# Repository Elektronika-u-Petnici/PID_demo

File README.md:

# PID demo

Ploča za demonstraciju uticaja parametara PID kontrolera.

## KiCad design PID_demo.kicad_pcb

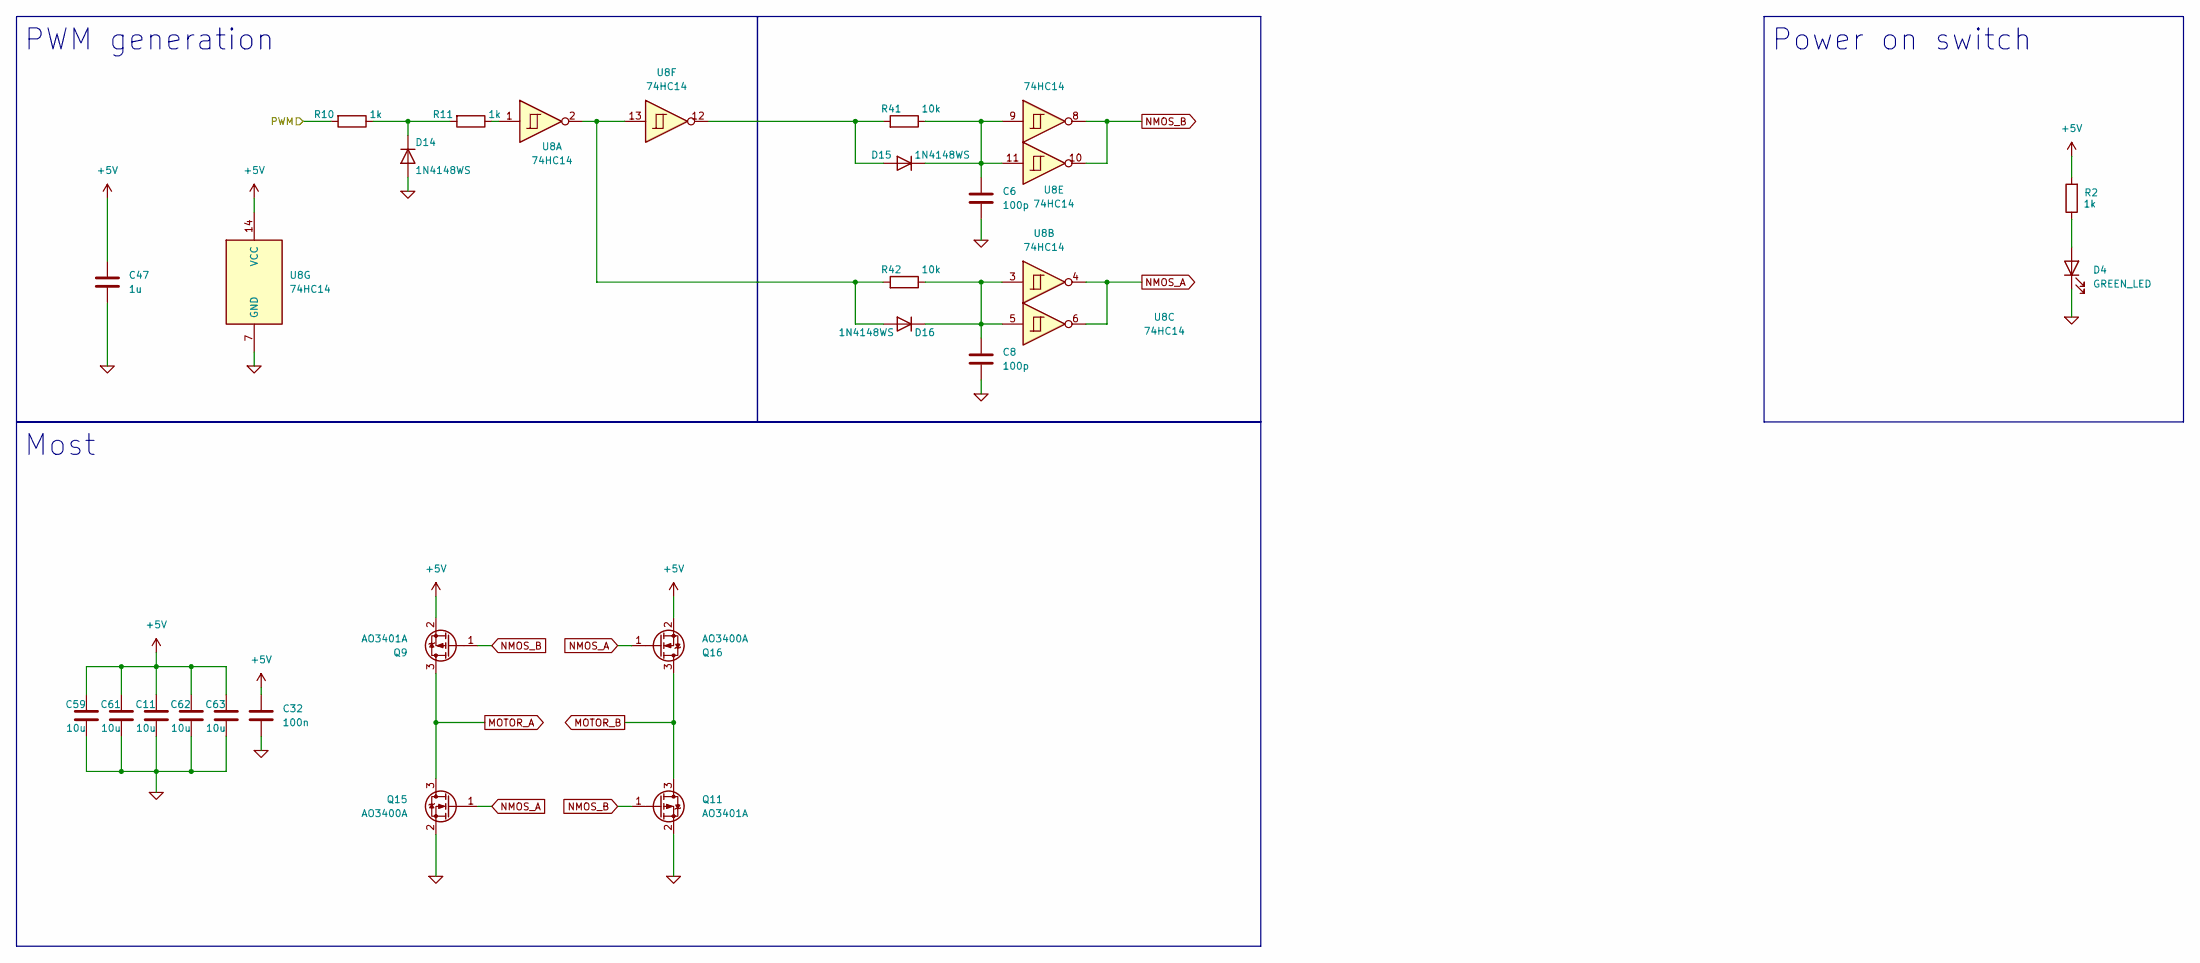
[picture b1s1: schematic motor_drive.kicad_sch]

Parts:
C6, C8: 100p; C_0603_1608Metric_Pad1.08x0.95mm_HandSolder; LCSC C14858
C11, C59, C61, C62, C63: 10u; R_0805_2012Metric_Pad1.20x1.40mm_HandSolder; Voltage 25V; LCSC C15850
C32: 100n; C_0603_1608Metric_Pad1.08x0.95mm_HandSolder; LCSC C14663
C47: 1u; C_0603_1608Metric_Pad1.08x0.95mm_HandSolder; LCSC C15849
D4: GREEN_LED; LED_0805_2012Metric_Pad1.15x1.40mm_HandSolder; LCSC C2297
D14, D15, D16: 1N4148WS; D_SOD-323; LCSC C2128
Q9, Q11: AO3401A; SOT-23; LCSC C15127
Q15, Q16: AO3400A; SOT-23; LCSC C20917
R2, R10, R11: 1k; R_0603_1608Metric_Pad0.98x0.95mm_HandSolder; LCSC C21190
R41, R42: 10k; R_0603_1608Metric_Pad0.98x0.95mm_HandSolder; LCSC C25804
U8: 74HC14; SOIC-14_3.9x8.7mm_P1.27mm

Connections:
0: C6.1, C8.1, C11.1, C32.1, C47.1, C59.1, C61.1, C62.1, C63.1, D4.1 (K), D14.2 (A), Q11.2 (S), Q15.2 (S), U8.7 (GND); also elsewhere on the board
+5V: C11.2, C32.2, C47.2, C59.2, C61.2, C62.2, C63.2, Q9.2 (S), Q16.2 (S), R2.2, U8.14 (VCC); also elsewhere on the board
/Motor drive/PWM: R10.2; also elsewhere on the board
MOTOR_A: Q9.3 (D), Q15.3 (D)
MOTOR_B: Q11.3 (D), Q16.3 (D)
NMOS_A: Q15.1 (G), Q16.1 (G), U8.4, U8.6
NMOS_B: Q9.1 (G), Q11.1 (G), U8.8, U8.10
unnamed: D4.2 (A), R2.1
unnamed: D14.1 (K), R10.1, R11.2
unnamed: D15.2 (A), R41.2, U8.12
unnamed: C6.2, D15.1 (K), R41.1, U8.9, U8.11
unnamed: D16.2 (A), R42.2, U8.2, U8.13
unnamed: C8.2, D16.1 (K), R42.1, U8.3, U8.5
unnamed: R11.1, U8.1

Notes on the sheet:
Power on switch
PWM generation
Most

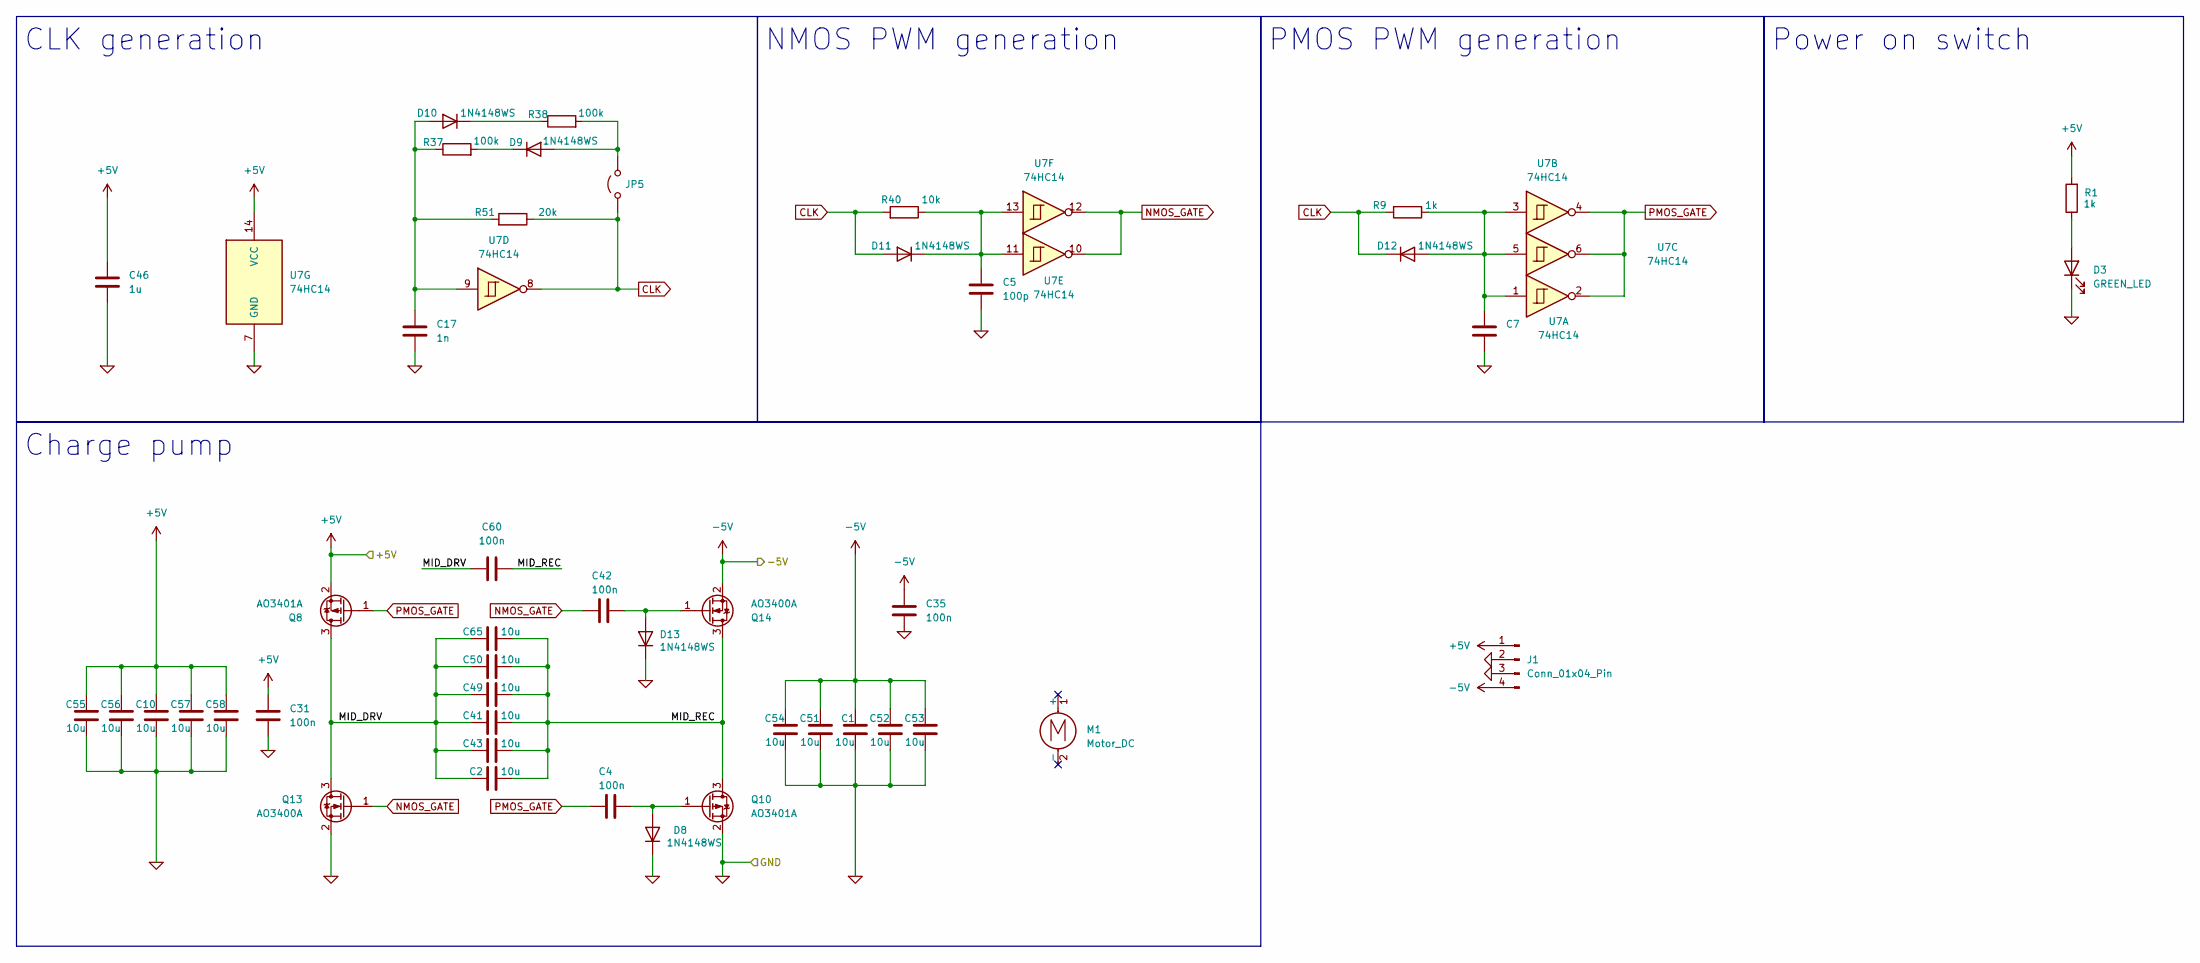
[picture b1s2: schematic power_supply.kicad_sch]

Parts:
C1, C2, C10, C41, C43, C49, C50, C51, C52, C53, C54, C55, C56, C57, C58, C65: 10u; R_0805_2012Metric_Pad1.20x1.40mm_HandSolder; Voltage 25V; LCSC C15850
C4, C31, C35, C42, C60: 100n; C_0603_1608Metric_Pad1.08x0.95mm_HandSolder; LCSC C14663
C5, C7: 100p; C_0603_1608Metric_Pad1.08x0.95mm_HandSolder; LCSC C14858
C17: 1n; C_0603_1608Metric_Pad1.08x0.95mm_HandSolder; LCSC C1588
C46: 1u; C_0603_1608Metric_Pad1.08x0.95mm_HandSolder; LCSC C15849
D3: GREEN_LED; LED_0805_2012Metric_Pad1.15x1.40mm_HandSolder; LCSC C2297
D8, D9, D10, D11, D12, D13: 1N4148WS; D_SOD-323; LCSC C2128
J1: Conn_01x04_Pin; PinHeader_1x04_P2.54mm_Vertical
JP5: Jumper_2_Open; SolderJumper-2_P1.3mm_Open_RoundedPad1.0x1.5mm
M1: Motor_DC; N20_motor
Q8, Q10: AO3401A; SOT-23; LCSC C15127
Q13, Q14: AO3400A; SOT-23; LCSC C20917
R1, R9: 1k; R_0603_1608Metric_Pad0.98x0.95mm_HandSolder; LCSC C21190
R37, R38: 100k; R_0603_1608Metric_Pad0.98x0.95mm_HandSolder; LCSC C25803
R40: 10k; R_0603_1608Metric_Pad0.98x0.95mm_HandSolder; LCSC C25804
R51: 20k; R_0603_1608Metric_Pad0.98x0.95mm_HandSolder; LCSC C4184
U7: 74HC14; SOIC-14_3.9x8.7mm_P1.27mm

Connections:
0: C1.1, C5.1, C7.1, C10.1, C17.1, C31.1, C35.1, C46.1, C51.1, C52.1, C53.1, C54.1, C55.1, C56.1, C57.1, C58.1, D3.1 (K), D8.1 (K), D13.1 (K), J1.2, J1.3, Q10.2 (S), Q13.2 (S), U7.7 (GND); also elsewhere on the board
+5V: C10.2, C31.2, C46.2, C55.2, C56.2, C57.2, C58.2, J1.1, Q8.2 (S), R1.2, U7.14 (VCC); also elsewhere on the board
-5V: C1.2, C35.2, C51.2, C52.2, C53.2, C54.2, J1.4, Q14.2 (S); also elsewhere on the board
/Charge pump/MID_DRV: C2.1, C41.1, C43.1, C49.1, C50.1, C60.2, C65.1, Q8.3 (D), Q13.3 (D)
/Charge pump/MID_REC: C2.2, C41.2, C43.2, C49.2, C50.2, C60.1, C65.2, Q10.3 (D), Q14.3 (D)
CLK: D11.2 (A), D12.1 (K), JP5.1 (A), R9.2, R40.2, R51.1, U7.8
NMOS_GATE: C42.1, Q13.1 (G), U7.10, U7.12
unnamed: D3.2 (A), R1.1
unnamed: C4.2, D8.2 (A), Q10.1 (G)
unnamed: D9.2 (A), JP5.2 (B), R38.2
unnamed: D9.1 (K), R37.2
unnamed: C17.2, D10.2 (A), R37.1, R51.2, U7.9
unnamed: D10.1 (K), R38.1
unnamed: C5.2, D11.1 (K), R40.1, U7.11, U7.13
unnamed: C7.2, D12.2 (A), R9.1, U7.1, U7.3, U7.5
unnamed: C42.2, D13.2 (A), Q14.1 (G)
PMOS_GATE: C4.1, Q8.1 (G), U7.2, U7.4, U7.6

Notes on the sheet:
Power on switch
Charge pump
CLK generation
NMOS PWM generation
PMOS PWM generation

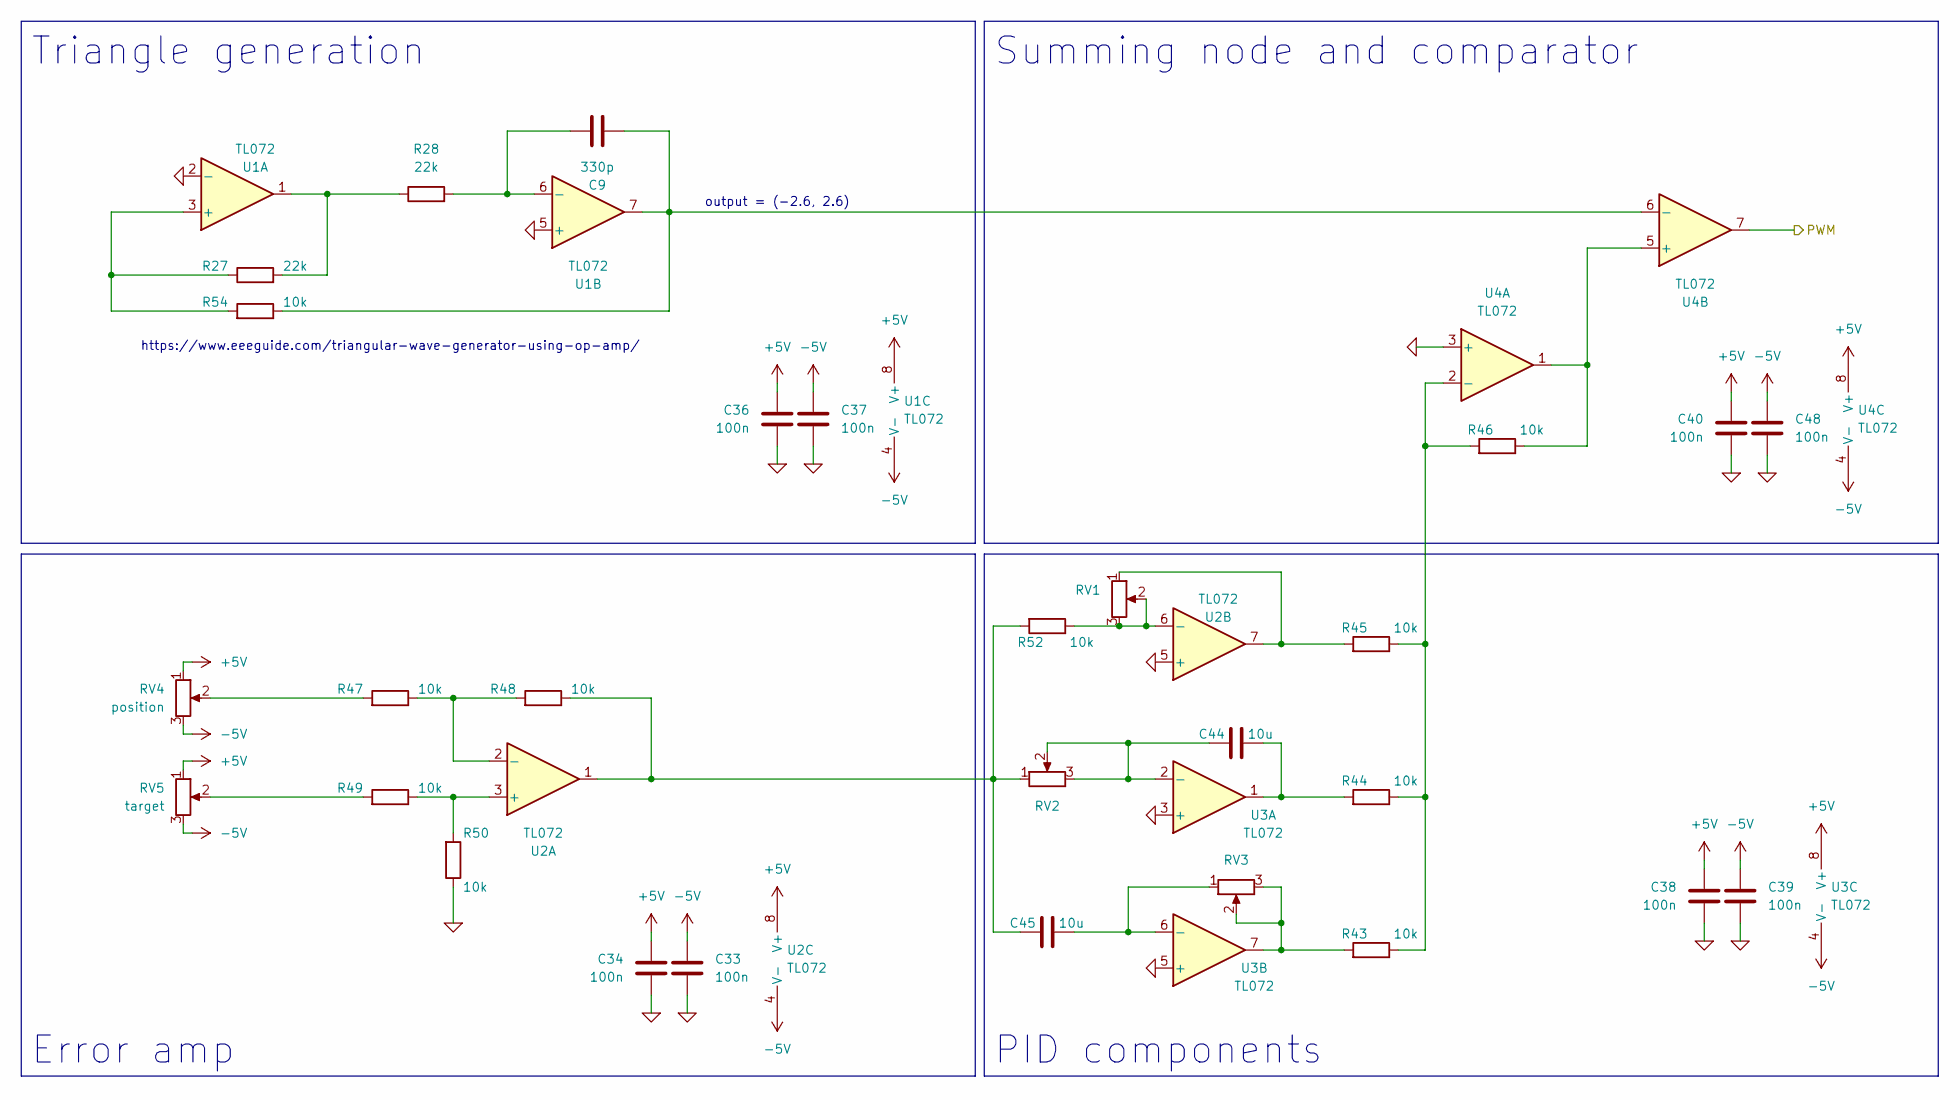
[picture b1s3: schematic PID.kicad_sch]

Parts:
C9: 330p; R_0603_1608Metric_Pad0.98x0.95mm_HandSolder; LCSC C1664
C33, C34, C36, C37, C38, C39, C40, C48: 100n; C_0603_1608Metric_Pad1.08x0.95mm_HandSolder; LCSC C14663
C44, C45: 10u; R_0805_2012Metric_Pad1.20x1.40mm_HandSolder; Voltage 25V; LCSC C15850
R27, R28: 22k; R_0603_1608Metric_Pad0.98x0.95mm_HandSolder; LCSC C31850
R43, R44, R45, R46, R47, R48, R49, R50, R52, R54: 10k; R_0603_1608Metric_Pad0.98x0.95mm_HandSolder; LCSC C25804
RV1, RV2, RV3: R_Potentiometer; front_plate_pot
RV4: position; front_plate_pot
RV5: target; front_plate_pot
U1, U2, U3, U4: TL072; SOIC-8_3.9x4.9mm_P1.27mm; LCSC C6961

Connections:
0: C33.1, C34.1, C36.1, C37.1, C38.1, C39.1, C40.1, C48.1, R50.1, U1.2 (-), U1.5 (+), U2.5 (+), U3.3 (+), U3.5 (+), U4.3 (+); also elsewhere on the board
+5V: C34.2, C36.2, C38.2, C40.2, RV4.1, RV5.1, U1.8 (V+), U2.8 (V+), U3.8 (V+), U4.8 (V+); also elsewhere on the board
-5V: C33.2, C37.2, C39.2, C48.2, RV4.3, RV5.3, U1.4 (V-), U2.4 (V-), U3.4 (V-), U4.4 (V-); also elsewhere on the board
/Motor drive/PWM: U4.7; also elsewhere on the board
unnamed: C44.2, R44.2, U3.1
unnamed: C45.1, R48.1, R52.2, RV2.1, U2.1
unnamed: R27.2, R28.1, U1.1
unnamed: R43.2, RV3.2, RV3.3, U3.7
unnamed: R45.2, RV1.1, U2.7
unnamed: R47.2, RV4.2
unnamed: R49.2, RV5.2
unnamed: R27.1, R54.2, U1.3 (+)
unnamed: C9.2, R28.2, U1.6 (-)
unnamed: R49.1, R50.2, U2.3 (+)
unnamed: R47.1, R48.2, U2.2 (-)
unnamed: R52.1, RV1.2, RV1.3, U2.6 (-)
unnamed: C44.1, RV2.2, RV2.3, U3.2 (-)
unnamed: C45.2, RV3.1, U3.6 (-)
unnamed: R43.1, R44.1, R45.1, R46.2, U4.2 (-)
unnamed: R46.1, U4.1, U4.5 (+)
unnamed: C9.1, R54.1, U1.7, U4.6 (-)

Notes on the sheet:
https://www.eeeguide.com/triangular-wave-generator-using-op-amp/
output = (-2.6, 2.6)
Error amp
Summing node and comparator
Triangle generation
PID components

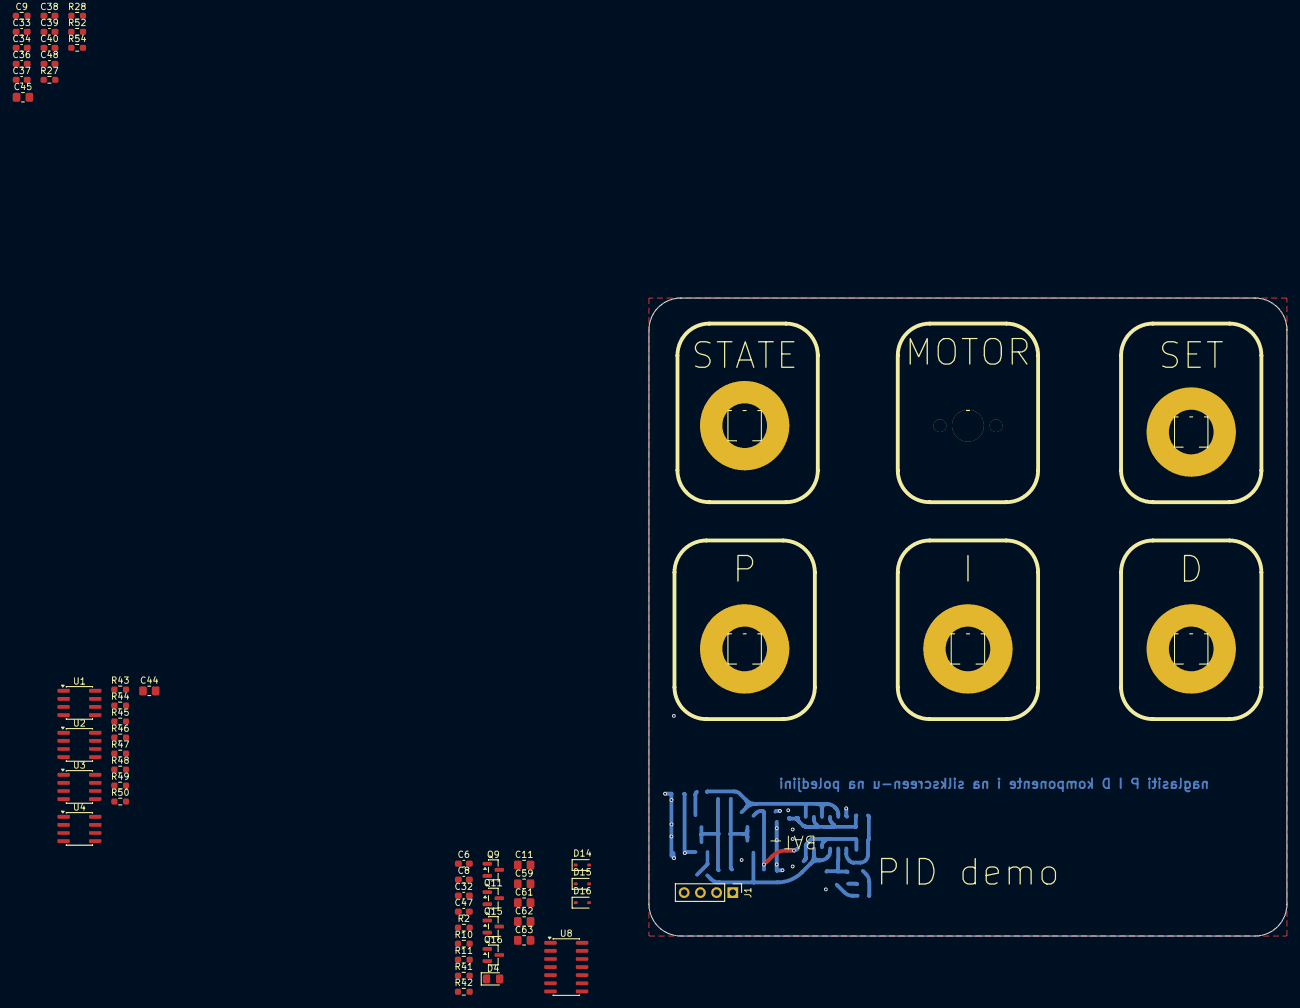
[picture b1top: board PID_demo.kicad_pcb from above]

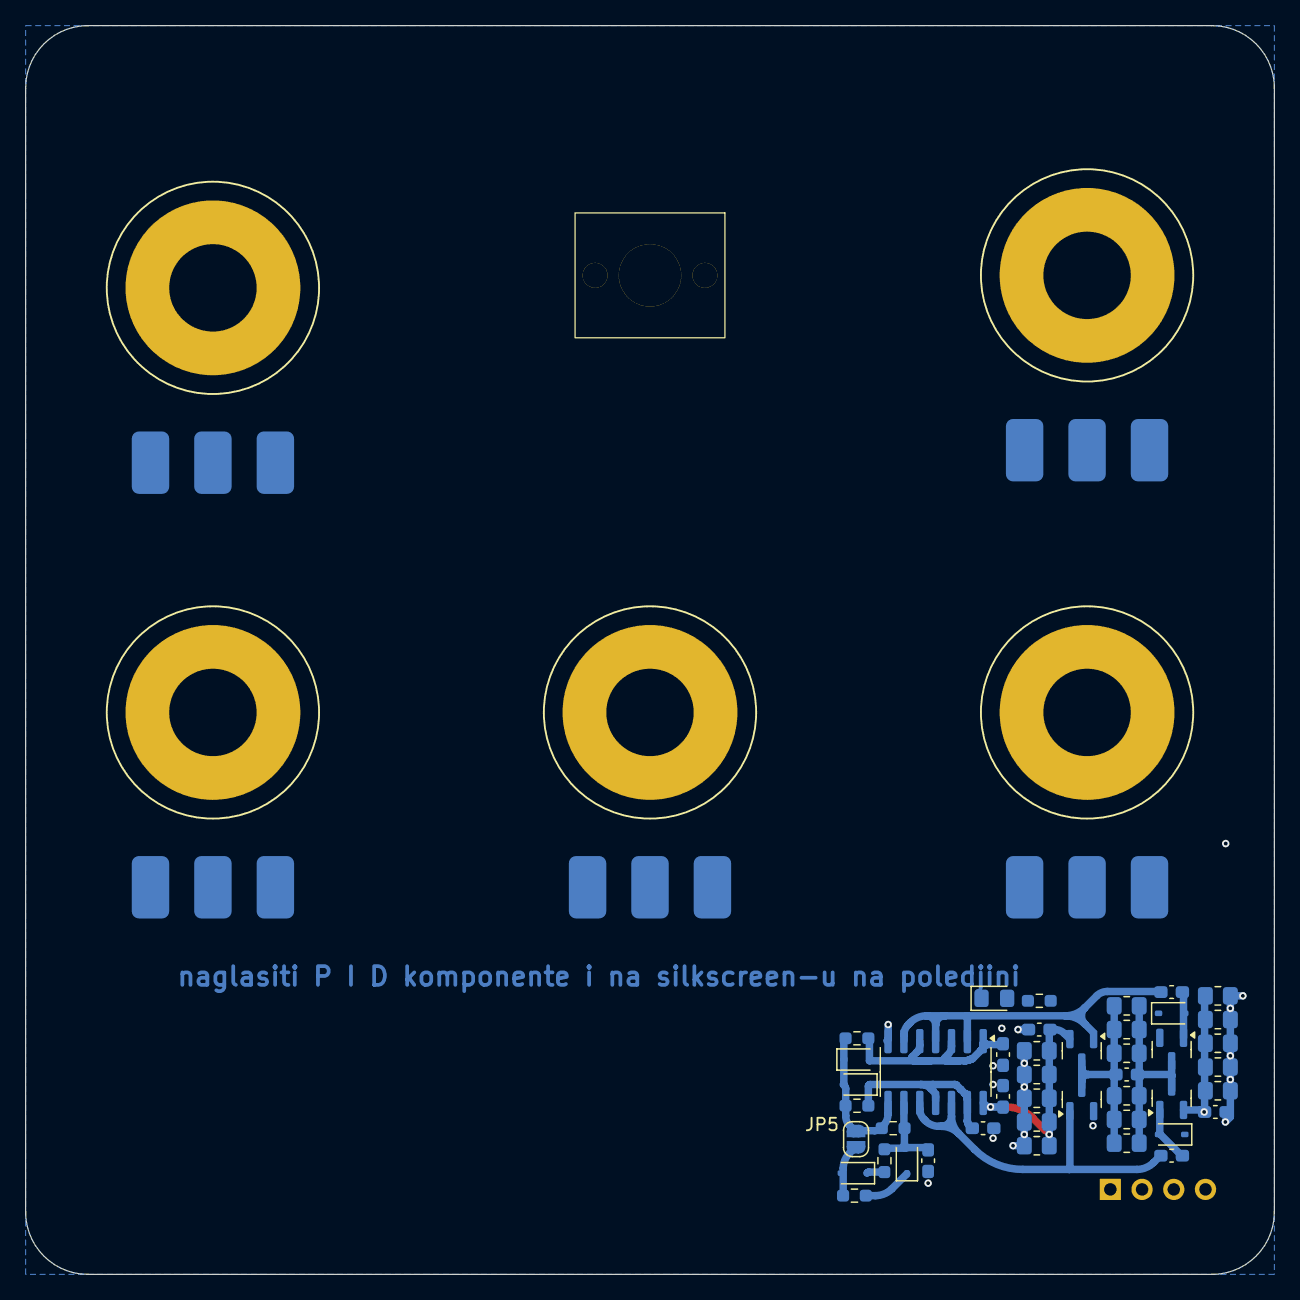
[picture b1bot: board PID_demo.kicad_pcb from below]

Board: 2 copper layers, 100.0 x 100.0 mm, 101 parts (44 on the bottom side), 46 nets.

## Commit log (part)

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2025-11-16 Init. Potentiometer placement.
2025-11-17 Added readme.
2025-11-18 Added motor 3d model.
